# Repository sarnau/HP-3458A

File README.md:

# HP-3458A

HP Keysight Agilent 3458A firmware and information. It is currently mostly containing the available PDF documentation and reverse engineering of the R9 firmware, plus documentation about the contents of the CALRAM.

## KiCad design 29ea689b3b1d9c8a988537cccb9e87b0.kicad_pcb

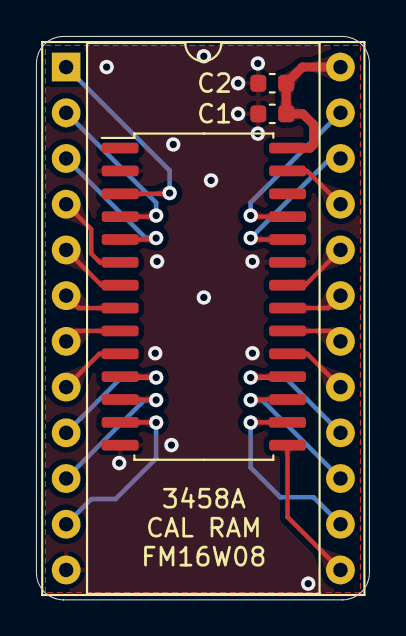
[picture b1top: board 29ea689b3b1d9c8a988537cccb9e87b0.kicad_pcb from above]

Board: 2 copper layers, 18.5 x 31.3 mm, 4 parts (0 on the bottom side), 24 nets.

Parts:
C1: 0.1u; C_0603_1608Metric
C2: 1u; C_0603_1608Metric
U1: DS1220; DIP-24_W15.24mm_Socket
U2: FM16W08-SG; SOIC-28W_7.5x17.9mm_P1.27mm

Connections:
/A0: U1.8 (A0), U2.10 (A0)
/A1: U1.7 (A1), U2.9 (A1)
/A2: U1.6 (A2), U2.8 (A2)
/A3: U1.5 (A3), U2.7 (A3)
/A4: U1.4 (A4), U2.6 (A4)
/A5: U1.3 (A5), U2.5 (A5)
/A6: U1.2 (A6), U2.4 (A6)
/A7: U1.1 (A7), U2.3 (A7)
/A8: U1.23 (A8), U2.25 (A8)
/A9: U1.22 (A9), U2.24 (A9)
/A10: U1.19 (A10), U2.21 (A10)
/D0: U1.9 (Q0), U2.11 (DQ0)
/D1: U1.10 (Q1), U2.12 (DQ1)
/D2: U1.11 (Q2), U2.13 (DQ2)
/D3: U1.13 (Q3), U2.15 (DQ3)
/D4: U1.14 (Q4), U2.16 (DQ4)
/D5: U1.15 (Q5), U2.17 (DQ5)
/D6: U1.16 (Q6), U2.18 (DQ6)
/D7: U1.17 (Q7), U2.19 (DQ7)
GND: C1.2, C2.2, U1.12 (GND), U2.2 (A12), U2.14 (VSS), U2.23 (A11)
unnamed: U1.18 (~CS), U2.20 (~CE)
unnamed: U1.20 (~OE), U2.22 (~OE)
unnamed: U1.21 (~WE), U2.27 (~WE)
VDD: C1.1, C2.1, U1.24 (VCC), U2.28 (VDD)

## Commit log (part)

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2025-08-02 16 bit alignment
2025-08-03 Some PSOS code
2025-08-04 Added all symbols
2025-08-04 More documentation
2025-08-04 More MATH code
2025-08-05 pSOS work
2025-08-06 A lot more work on the code
2025-08-06 More CALRAM stuff, more IRQ code
2025-08-06 More work on the keyboard
2025-08-06 More work
2025-08-07 SETTINGS
2025-08-09 Adding tokens and 68k code generation labels
2025-08-09 More work on CALRAM
2025-08-09 CALRAM with calibration and the empty CAMRAL from the ROM
2025-08-09 Folder cleanup
2025-08-10 More firmware work
2025-08-10 CALRAM dump
2025-08-10 More documents
2025-08-10 Memory map cleanup
2025-08-11 Adding datasheets for ICs
2025-08-11 Documenting the memory map
2025-08-11 Work on timer, etc
2025-08-11 More BASIC work
2025-08-12 More work on tokens
2025-08-12 More work on error handling
2025-08-13 More work (frontpanel stuff)
2025-08-13 Datasheets
2025-08-17 Adding the original firmware of my 3458A
2025-08-17 Adding oldest known firmware
2025-08-18 Update a datasheets
2025-08-18 Removed unnecessary data sheet
2025-08-18 Firmware cleanup
2025-08-18 ROM Checksum, Delays commented
2025-08-18 Working on memory mappings
2025-08-18 Dumping the two PALs for address decoding
2025-08-18 PAL code
2025-08-18 Fixing the missing info SHEET 2/2 of the Outguard Controller Board
    SHEET 2/2 of the Outguard Controller Board was copied without important informations: significant parts of the wiring to the ICs U603, U900 and U901. I have traced the lines and patched the diagram
2025-08-19 Memory map is done
2025-08-19 Added labels for simulator code
2025-08-19 Adding Ghidra 11.4.1 Motorola 68000 Processor Files
2025-08-19 Log which areas of the CALRAM are used by which calibration
2025-08-20 Support printing the initial calibration (from ROM)
2025-08-20 Document the ENABLE and STATUS HW Register
2025-08-21 Update memory info to markdown tables
2025-08-22 Annuc
2025-08-22 More memory map clarification
2025-09-02 Buffer work
2025-09-06 More work on the internal communication
2025-09-11 Keycommands
